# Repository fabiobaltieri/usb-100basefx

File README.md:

USB to 100BASE-FX
==================

http://fabiobaltieri.com/2013/05/26/usb-to-100base-fx-optical-fiber-network-card/

This project is an Open-Hardware USB to 100BASE-FX fiber optic network card,
based on an ASIX AX88772B USB to Fast Ethernet controller, and comes in two
variants for the fiber transciver.

License
-------

This work is licensed under a Creative Commons Attribution-ShareAlike 3.0
License.

Contents
--------

    README        this file
    docs/         datasheets and documentation
    scsc/         source directory for the 1x9 hardware variant
    sfp/          source directory for the SFP hardware variant
    eeprom-notes  some notes and snippets on device configuration

Hardware
--------

All hardware files (schematic, layout and libraries) are in CadSoft Eagle
format.

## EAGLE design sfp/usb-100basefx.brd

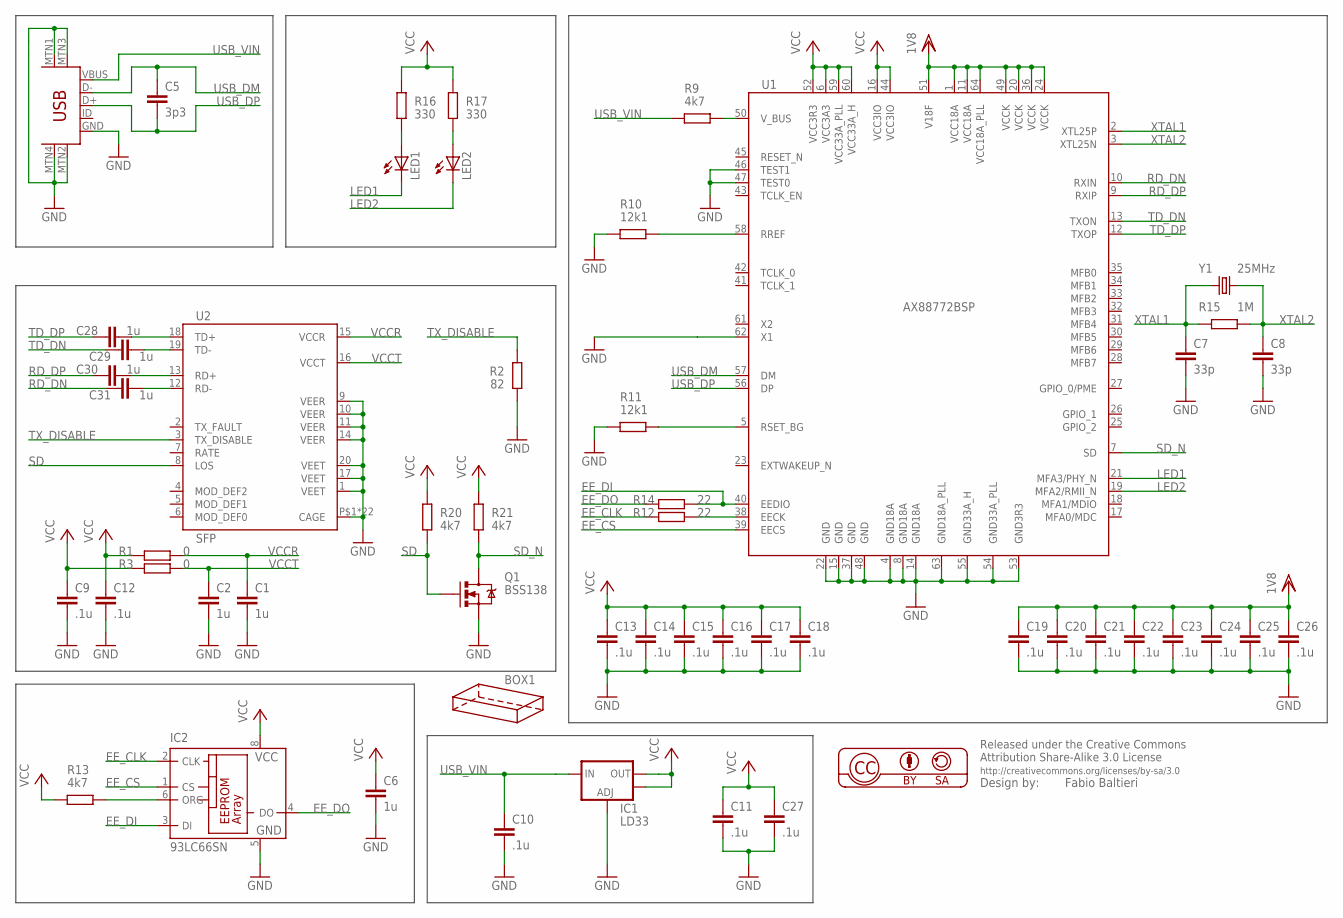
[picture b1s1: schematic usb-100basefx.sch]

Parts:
BOX1: HAMMOND-BOX-H-1H; 1551H-1HOLE
C1, C2, C6, C28, C29, C30, C31: 1u; C0603
C5: 3p3; C0603
C7, C8: 33p; C0603
C9, C10, C11, C12, C13, C14, C15, C16, C17, C18, C19, C20, C21, C22, C23, C24, C25, C26, C27: .1u; C0603
IC1: LD33; SOT223
IC2: 93LC66SN; SO-08
LED1, LED2: LEDCHIPLED_0805; CHIPLED_0805
Q1: BSS138; SOT23
R1, R3: 0; R0603
R2: 82; R0603
R9, R13, R20, R21: 4k7; R0603
R10, R11: 12k1; R0603
R12, R14: 22; R0603
R15: 1M; R0603
R16, R17: 330; R0603
U1: AX88772BSP; LQFP64-0.4MM-SHORTPAD
U2: SFP
U$1: USB-MINIB-5PIN; USB-MINIB
Y1: 25MHz; CRYSTAL-SMD-5X3

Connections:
EE_CLK: IC2.2 (CLK), R12.1
EE_CS: IC2.1 (CS), U1.39 (EECS)
EE_DI: IC2.3 (DI), R14.2, U1.40 (EEDIO)
EE_DO: IC2.4 (DO), R14.1
GND: C1.2, C2.2, C6.2, C7.2, C8.2, C9.2, C10.2, C11.2, C12.2, C13.2, C14.2, C15.2, C16.2, C17.2, C18.2, C19.2, C20.2, C21.2, C22.2, C23.2, C24.2, C25.2, C26.2, C27.2, IC1.1 (ADJ), IC2.5 (GND), Q1.2 (S), R2.2, R10.1, R11.1, U1.4 (GND18A), U1.8 (GND18A), U1.14 (GND18A), U1.15 (GND), U1.22 (GND), U1.37 (GND), U1.46 (TEST1), U1.47 (TEST0), U1.48 (GND), U1.53 (GND3R3), U1.54 (GND33A_PLL), U1.55 (GND33A_H), U1.62 (X1), U1.63 (GND18A_PLL), U2.1 (VEET), U2.9 (VEER), U2.10 (VEER), U2.11 (VEER), U2.14 (VEER), U2.17 (VEET), U2.20 (VEET), U2.P$1 (CAGE), U2.P$2 (CAGE), U2.P$3 (CAGE), U2.P$4 (CAGE), U2.P$5 (CAGE), U2.P$6 (CAGE), U2.P$7 (CAGE), U2.P$8 (CAGE), U2.P$9 (CAGE), U2.P$10 (CAGE), U2.P$11 (CAGE), U2.P$12 (CAGE), U2.P$13 (CAGE), U2.P$14 (CAGE), U2.P$15 (CAGE), U2.P$16 (CAGE), U2.P$17 (CAGE), U2.P$18 (CAGE), U2.P$19 (CAGE), U2.P$20 (CAGE), U2.P$21 (CAGE), U2.P$22 (CAGE), U$1.GND, U$1.MTN1 (MTN2), U$1.MTN2 (MTN3), U$1.MTN3 (MTN1), U$1.MTN4
LED1: LED1.C, U1.21 (MFA3/PHY_N)
LED2: LED2.C, U1.19 (MFA2/RMII_N)
unnamed: R9.2, U1.50 (V_BUS)
unnamed: R10.2, U1.58 (RREF)
unnamed: R11.2, U1.5 (RSET_BG)
unnamed: R12.2, U1.38 (EECK)
unnamed: IC2.6 (ORG), R13.2
unnamed: LED1.A, R16.2
unnamed: LED2.A, R17.2
unnamed: C29.2, U2.19 (TD-)
unnamed: C28.2, U2.18 (TD+)
unnamed: C30.2, U2.13 (RD+)
unnamed: C31.2, U2.12 (RD-)
RD_DN: C31.1, U1.10 (RXIN)
RD_DP: C30.1, U1.9 (RXIP)
SD: Q1.1 (G), R20.2, U2.8 (LOS)
SD_N: Q1.3 (D), R21.2, U1.7 (SD)
TD_DN: C29.1, U1.13 (TXON)
TD_DP: C28.1, U1.12 (TXOP)
TX_DISABLE: R2.1, U2.3 (TX_DISABLE)
USB_DM: C5.1, U1.57 (DM), U$1.D-
USB_DP: C5.2, U1.56 (DP), U$1.D+
USB_VIN: C10.1, IC1.3 (IN), R9.1, U$1.VBUS
VCC: C6.1, C9.1, C11.1, C12.1, C13.1, C14.1, C15.1, C16.1, C17.1, C18.1, C27.1, IC1.2 (OUT), IC1.4 (OUT), IC2.8 (VCC), R1.1, R3.1, R13.1, R16.1, R17.1, R20.1, R21.1, U1.6 (VCC3A3), U1.16 (VCC3IO), U1.44 (VCC3IO), U1.52 (VCC3R3), U1.59 (VCC33A_PLL), U1.60 (VCC33A_H)
VCCR: C1.1, R1.2, U2.15 (VCCR)
VCCT: C2.1, R3.2, U2.16 (VCCT)
VDD: C19.1, C20.1, C21.1, C22.1, C23.1, C24.1, C25.1, C26.1, U1.1 (VCC18A), U1.11 (VCC18A), U1.20 (VCCK), U1.24 (VCCK), U1.36 (VCCK), U1.49 (VCCK), U1.51 (V18F), U1.64 (VCC18A_PLL)
XTAL1: C7.1, R15.1, U1.2 (XTL25P), Y1.1
XTAL2: C8.1, R15.2, U1.3 (XTL25N), Y1.3 (2)

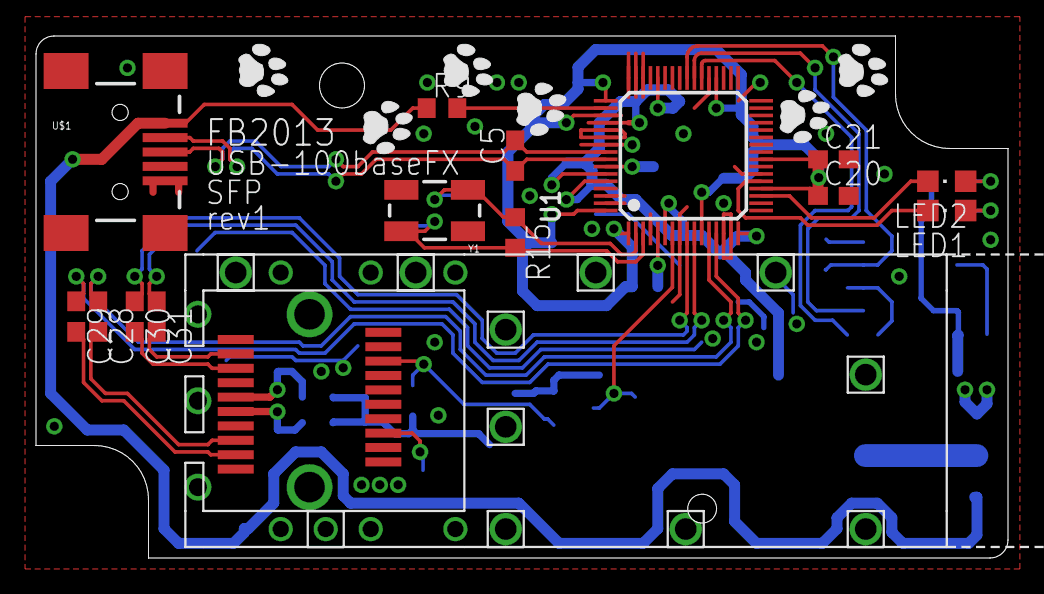
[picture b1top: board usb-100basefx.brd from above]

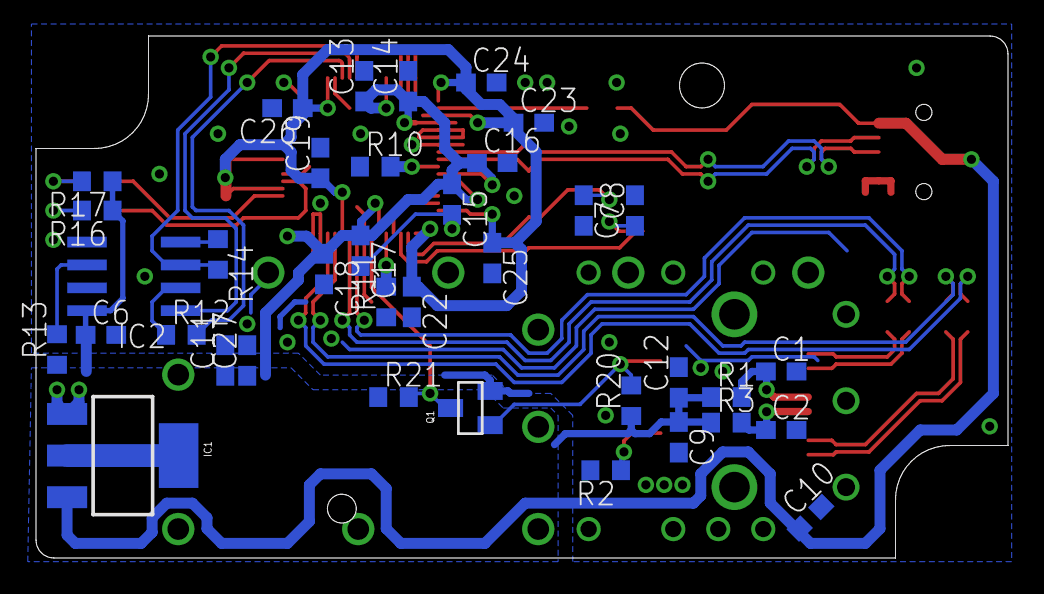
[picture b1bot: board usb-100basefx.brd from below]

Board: 2 copper layers, 54.0 x 29.0 mm, 59 parts (37 on the bottom side), 34 nets.

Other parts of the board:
U$2, U$4, U$8: CAT-L
U$3, U$5, U$7: CAT-R

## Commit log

2012-12-04 hw: use ld1117 for power
2012-12-09 move usb connector
2012-12-15 move scsc version to scsc directory
2013-01-16 hw-scsc: add some more gnd vias
2013-01-19 hw: redone
2013-01-19 hw: rcx
2013-01-20 rc: update
2013-03-16 hw: change some values
2013-03-16 notes: add eeprom notes
2013-03-16 docs: add some documentation
2013-03-31 add sfp version
2013-03-31 add gitignore file
2013-03-31 sfp: fixes
2013-03-31 add gnd guard
2013-03-31 drill to 1.6mm
2013-03-31 there's a cat on my pcb...
2013-04-04 rev1: fix sd signal logic level
2013-04-04 sfp: schematic cleanup
2013-04-04 add some vias and close a ground plane
2013-05-25 sfp: change cap to 33p
2013-05-25 sfp: add bias note
2013-05-25 scsc: add pdf schematics
2013-05-25 sfp: add pdf schematics
2013-05-26 sfp: reword biasing note
2013-11-17 add README

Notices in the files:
parts and their libraries:
SparkFun-Connectors: Licensing: CC v3.0 Share-Alike You are welcome to use this library for commercial purposes.
balto: Released under the Creative Commons
balto: http://creativecommons.org/licenses/by-sa/3.0
